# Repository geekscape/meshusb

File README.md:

meshusb
==========

MeshUSB hardware and documentation repository.
-----------
The MeshUSB board is a USB to serial companion to any XBee-style form factor radio board, such as the MeshThing variants.

Current version is v0.3.

Contents:
-----------
-Hardware - Source files for PCB production.
-Resources - Additional documentation.
-Reference - Mostly datasheets.

Warnings:
-----------
*Reverse polarity on either the battery or auxilliary battery inputs are a potential battery fire danger.
*Over-voltage on the auxilliary charging input has potential to damage the board.

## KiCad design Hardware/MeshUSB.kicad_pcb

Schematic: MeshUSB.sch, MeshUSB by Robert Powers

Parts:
C3, C4, C9, C30: 100n
D1: RX_LED
D2: TX_LED
D5: LED
D6: ZENER
D7: DIODE-NC
D30: DUAL_SHOTTKEY_PACKAGE
F1: FUSE
Fi1, Fi2, Fi3: CONN_1
H1: XBeeLeftPins
H2: XBeeRightPins
JP1, JP3, JP4: JUMPER
JP2, JP5: CONN_TH_JMPR_DEFAULTCLOSED
Li-Battery1: BAT2
P1: USB_4
P2: PVCell
P30: JST_2
P31: CONN_1
Q1: MOS_P
Q2: MOS_P-INFINEON-BSS83P
R1, R2: 22R
R4: 33k
R5: 20k
R8, R9, R10: 270R
R30: 16R
U1: XBEE
U2: AP7313-3.3VREGULATOR
U4: FT231X-SSOP
U5: LTC4070
VR1, VR2: VR0603

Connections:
/BatConn+: JP5.2, Li-Battery1.1, P30.2 (PM)
/CC1: D30.3, R30.1
/Charge+: C30.1, D7.1 (K), JP5.1, Q1.2, Q2.2, R30.2, U5.2 (NTC), U5.8 (VCC)
/PV+: D30.2, P2.2 (PM)
/USBPwrIn: F1.1, P1.4 (GNDUSB)
BAT+: H1.1, U2.2
GND: C3.2, C4.2, C30.2, D6.1 (A), D7.3 (A), H1.10, Li-Battery1.2, P1.1 (VUSB), P2.1, P30.1, Q2.3, R10.1, U2.3, U4.6 (GND), U4.16 (GND), U5.5 (GND), U5.9 (PAD), VR1.2, VR2.2
unnamed: C9.1, JP2.1
unnamed: C9.2, U4.1 (~DTR)
unnamed: D1.1 (A), R8.2
unnamed: D1.2 (K), U4.17 (CBUS1)
unnamed: D2.1 (A), R9.2
unnamed: D2.2 (K), U4.10 (CBUS2)
unnamed: D5.2 (K), R10.2
unnamed: H1.2, U4.4 (RXD)
unnamed: H1.3, U4.20 (TXD)
unnamed: H1.5, JP2.2
unnamed: H2.1, JP4.1
unnamed: H2.7, JP3.1
unnamed: H2.8, JP1.1
unnamed: P1.2 (D-), R2.1, VR1.1
unnamed: P1.3 (D+), R1.1, VR2.1
unnamed: P31.1, U5.3 (ADJ)
unnamed: Q1.1, U5.6 (LBO)
unnamed: Q1.3, R4.2, U2.1
unnamed: Q2.1, U5.7 (DRV)
unnamed: R1.2, U4.12 (USBDM)
unnamed: R2.2, U4.11 (USBDP)
USB_VDD: C3.1, D6.2 (K), D30.1, F1.2, R8.1, R9.1, U4.15 (VCC)
VCCIO: C4.1, U4.3 (VCCIO), U4.13 (3v3OUT), U4.14 (~RESET)
_MT_PE4: JP4.2, R5.2
_MT_PF2: D5.1 (A), JP1.2, U5.4 (HBO)
_MT_PF3: JP3.2, R4.1, R5.1

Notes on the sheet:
MTTF Max Power can be set to allow for up to 500mA on the USB bus. 200mA is probably the max recommended - shouldn't need more under any circumstances. Default stays at 90mA for now.
ADJ -> Vcc= 4.2v Vout. ADJ -> NC=4.1v Vout. ADJ -> GND=4.0v Vout.
Charge Full Indicator... ...Active High! Seems this doesn't light when MT is inserted, think this should be fixed by changes to charging diodes.
R3 chosen to limit shunt current to 50mA. (4.5v-3.2v)/10=130mA max charge current. (4.5v-3.2v)^2/10=169mW PwrDiss (4.5v-4.1v)/40=mA max shunt current.
Conn_10s are for the smd headers in case I don't get around to incorporating them in a 20 pin xbee ff footprint.
PMOS1 does Low Battery cutoff.
Fw Drop Approx. 0.2V @ 100mA 0.3V @ 500mA
Still TODO for v0.3: Layout Fiducials. Jumpers for... what needs jumpers? Something must. Cutoff battery charging. Charge full indicator? Tx/Rx LEDs? USB vdd? Test points? Jump pads for 4070 AJD?
Charging max values charge I - 125mA=1C battery PwrDiss - 2W - depends on R30 shunt I - 50 mA
Exposed pins for charging... User must be careful! Do these as JST 2mm? Yes.
V.Div. Gives limited range. Get numbers from spreadsheet.
Approx. 6V max. without further current limiting. Diode forward current max. is 500mA.
This is for disabling soft reset ~DTR. Make as two .254mm THs connected by default.

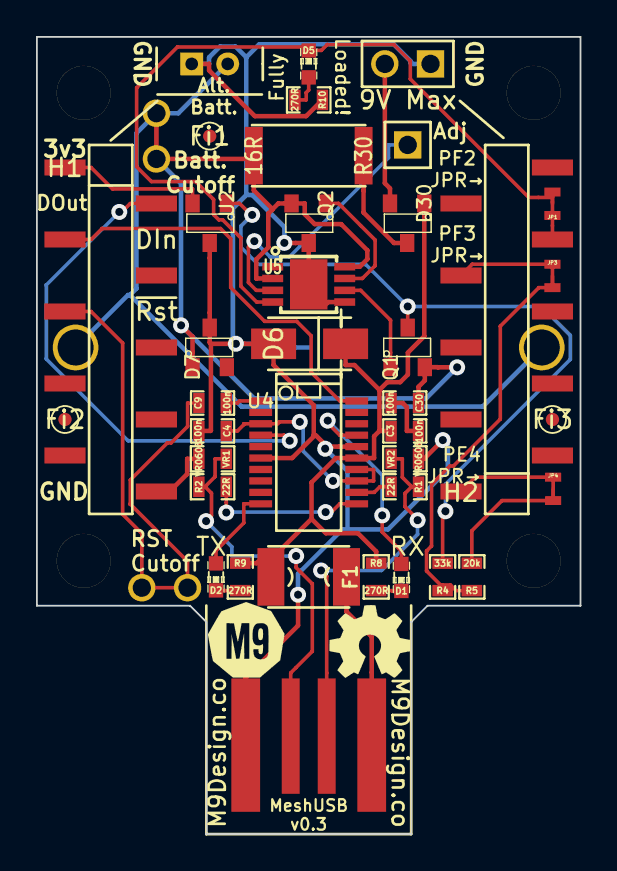
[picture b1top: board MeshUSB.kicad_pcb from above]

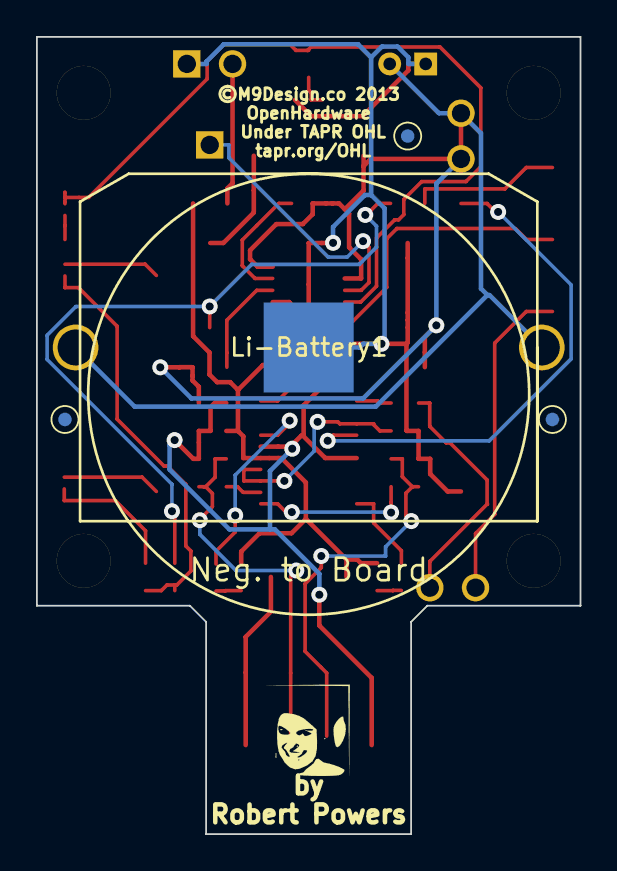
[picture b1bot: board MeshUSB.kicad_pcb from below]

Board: 2 copper layers, 30.2 x 44.3 mm, 49 parts (2 on the bottom side), 33 nets.

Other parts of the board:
1PIN1, 1PIN2, 1PIN3, 1PIN4: P***; _MUSB_3mmTH-1pin
G0, G1: LOGO
VAL: M9Logo-scaled

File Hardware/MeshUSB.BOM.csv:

Designator	Package	Quantity	Designation	Supplier and ref
C3,C4,C9,C30	SM0603_Capa	4	100n	
D1	LED-0603	1	RX_LED	
D2	LED-0603	1	TX_LED	
D30	SOT23	1	DUAL_SHOTTKEY_PACKAGE	
D5	LED-0603	1	LED	
D6	SMAZ5V6-Zener-DO214	1	ZENER	
D7	SOT23	1	DIODE-NC	
F1	MF-MSMF050-Fuse	1	FUSE	
Fi1,Fi2,Fi3	Fiducial	3	CONN_1	
H1	_MUSB-FEMALE-HEADER-NPPN101BFLD-RC-Pin1Right	1	XBeeLeftPins	
H2	_MUSB-FEMALE-HEADER-NPPN101BFLC-RC-Pin1Left	1	XBeeRightPins	
Li-Battery1	MPD-BK-5033_2450BatteryHolder	1	BAT2	
Q1	SOT23	1	MOS_P	
Q2	SOT23	1	MOS_P-INFINEON-BSS83P	
R1,R2	SM0603_Resistor	2	22R	
R30	TE3521-Series_Resistor-6.3x3.2	1	16R	
R4	SM0603_Resistor	1	33k	
R5	SM0603_Resistor	1	20k	
R8,R9,R10	SM0603_Resistor	3	270R	
U2	SOT23	1	AP7313-3.3VREGULATOR	
U4	SSOP20-FT231X	1	FT231X-SSOP	
U5	SSOP8-9	1	LTC4070	
VR1,VR2	SM0603_Resistor	2	VR0603

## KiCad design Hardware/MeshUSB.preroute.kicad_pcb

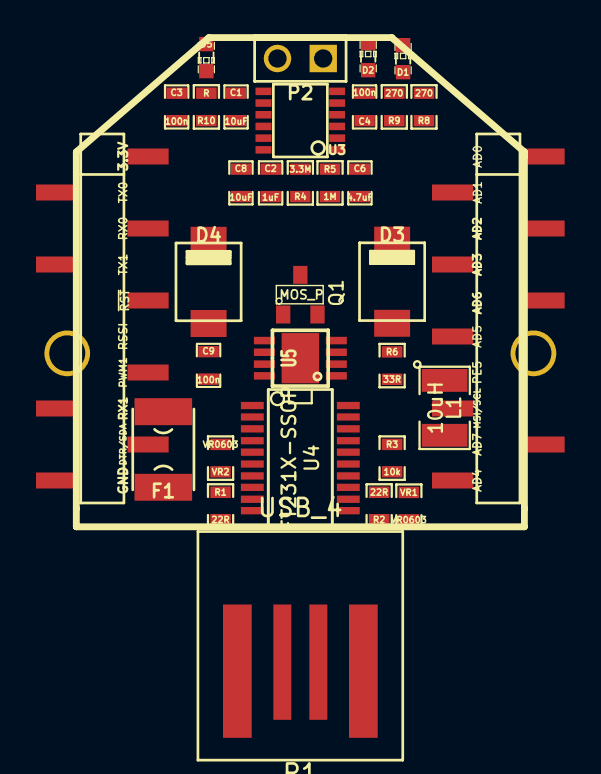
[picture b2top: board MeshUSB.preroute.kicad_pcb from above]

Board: 2 copper layers, 35 parts (1 on the bottom side), 29 nets, no tracks yet.

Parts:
C1, C8: 10uF; _MUSB_SM0603_Capa
C2: 1uF; _MUSB_SM0603_Capa
C3, C4, C9: 100n; _MUSB_SM0603_Capa
C6: 4.7uF; _MUSB_SM0603_Capa
D1: RX_LED; _MUSB_LED-0603
D2: TX_LED; _MUSB_LED-0603
D3, D4: DIODESCH; _MUSB_DO-214BA-Schottky
D5: LED; _MUSB_LED-0603
F1: FUSE; _MUSB_MF-MSMF050-Fuse
H1: XBeeLeftPins; _MUSB-FEMALE-HEADER-NPPN101BFLC-RC
H2: XBeeRightPins; _MUSB-FEMALE-HEADER-NPPN101BFLC-RC
L1: 10uH; SM1210
Li-Battery1: BAT2; _MUSB_MPD-BK-5033_2450BatteryHolder
P1: USB_4; _MUSB_USB-A-PCB
P2: PVCell; PIN_ARRAY_2X1
Q1: MOS_P; SOT23
R1, R2: 22R; _MUSB_SM0603_Resistor
R3: 10k; _MUSB_SM0603_Resistor
R4: 3.3M; _MUSB_SM0603_Resistor
R5: 1M; _MUSB_SM0603_Resistor
R6: 33R; _MUSB_SM0603_Resistor
R8, R9: 270; _MUSB_SM0603_Resistor
R10: R; _MUSB_SM0603_Resistor
U1: XBEE; _MUSB_XBee_Board_NO_PADS
U3: LTC3105-MSOP12; _MUSB_MSOP12
U4: FT231X-SSOP; SSOP20
U5: LTC4070; SSOP8-9
VR1, VR2: VR0603; _MUSB_SM0603_Resistor

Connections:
BAT+: H1.1, Q1.3
GND: C1.2, C2.2, C3.2, C4.2, C6.2, C8.2, Li-Battery1.2, P1.4, P2.1, R5.2, R10.1, U3.3, U3.5, U3.6, U3.7, U4.6, U4.16, U5.5, U5.9, VR1.2, VR2.2
unnamed: C9.1, H1.5
unnamed: C9.2, U4.1
unnamed: D2.2, U4.10
unnamed: D1.2, U4.17
unnamed: D2.1, R9.2
unnamed: D1.1, R8.2
unnamed: R3.2, U4.14
unnamed: R2.2, U4.11
unnamed: R1.2, U4.12
unnamed: H1.3, U4.20
unnamed: H1.2, U4.4
unnamed: F1.1, P1.1
unnamed: P1.3, R2.1, VR1.1
unnamed: P1.2, R1.1, VR2.1
unnamed: D5.2, R10.2
unnamed: D3.2, R6.1
unnamed: C8.1, D4.1, R4.1, U3.11
unnamed: C6.1, U3.2
unnamed: D4.2, Li-Battery1.1, Q1.2, R6.2, U5.2, U5.8
unnamed: Q1.1, U5.6
unnamed: D5.1, U5.4
unnamed: L1.2, U3.9
unnamed: C2.1, U3.12
unnamed: C1.1, L1.1, P2.2, U3.8
unnamed: R4.2, R5.1, U3.1
USB_VDD: C3.1, D3.1, F1.2, R3.1, U4.15
VCCIO: C4.1, R8.1, R9.1, U4.3, U4.13

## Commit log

2013-10-05 Initial v0.1 final commit. Moving to v0.2 from here.
2013-10-05 Getting moving on v0.2 :)
2013-10-09 More changes on list to v0.2.
2013-10-10 Moving away from LTC310X DCDC converters.
2013-10-12 Almost everything on the TODO is done. Layout done.
2013-10-12 Additional trace to connect everything even in the event the battery holder is not in place.
2013-10-12 Fixed minor pad spacing error on FT231X non-standard SSOP20 package.
2013-10-12 It is probably best to not leave that pin unconnected.
2013-10-14 Added mounting holes, some SMT jumpers and a voltage divider. Extended board for mounts by 3.5mm.
2013-10-18 Back.
2013-10-18 gitignore.
2013-10-18 Removing Archive folder from git tracking.
2013-10-18 Cleaning up.
2013-10-22 Change all the things\!
2013-10-22 Add files.
2013-12-05 TAPR Hardware License added.
2013-12-05 Added reference documents back.
2014-02-07 Mark for changes for v0.3.
2014-02-19 Begin major modifications for post v0.2.
2014-02-20 Begin Layout. Still some schematic additions required.
2014-02-21 Further changes. Still looking for appropriate diode and PMOS packages.
2014-02-22 Schematic notes and library updates.
2014-02-23 .gitignore kicad-bak
2014-02-23 Higher current charging. Some datasheets.
2014-02-24 Almost to layout. Charging slightly modified, confirming BOM.
2014-02-24 Layoutsplosion.
2014-02-24 Layout positions nearly finalized.
2014-02-24 Further placements, silks, refs. Next:Double check all pins and packages.
2014-02-24 Routed. In need of further review and a few more TODOs.
2014-02-26 Layout & routing nearly final. Current carrying trace widths need to be embiggened.
2014-02-26 Adding nets.
2014-02-26 Embiggining and reroute done. Double checks on pad-connect traces and via placements next.
2014-02-27 Final touches, render, update some datasheets.
2014-02-27 More render and datasheets.
2014-02-28 V0.3 Production ready. This version sent for quote. TODO: Placements.
2014-03-05 Positions and minor silk.
2014-03-05 Minor render update
2014-03-06 V0.3 production files.
2014-04-29 Readme updates.
2014-05-02 Updated schematic notes and cleaned up library inconsistencies due to KiCAD version upgrade.

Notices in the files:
Hardware/MeshUSB.kicad_pcb:
©M9Design.co 2013
